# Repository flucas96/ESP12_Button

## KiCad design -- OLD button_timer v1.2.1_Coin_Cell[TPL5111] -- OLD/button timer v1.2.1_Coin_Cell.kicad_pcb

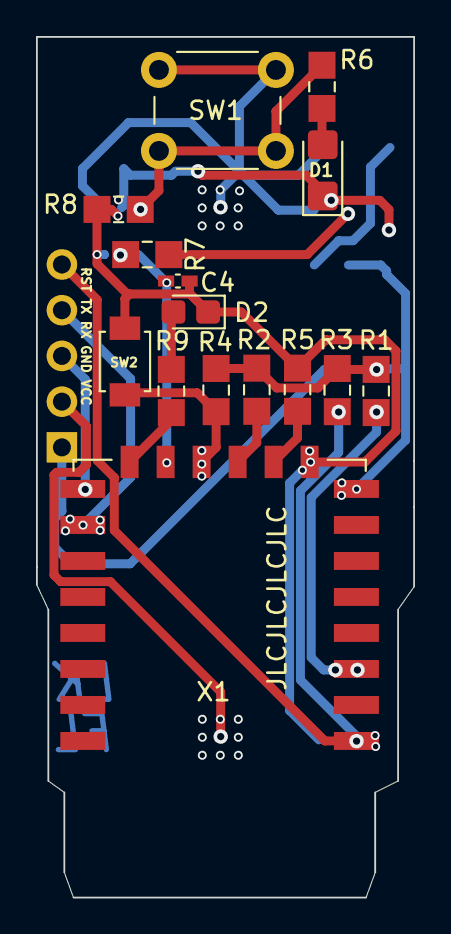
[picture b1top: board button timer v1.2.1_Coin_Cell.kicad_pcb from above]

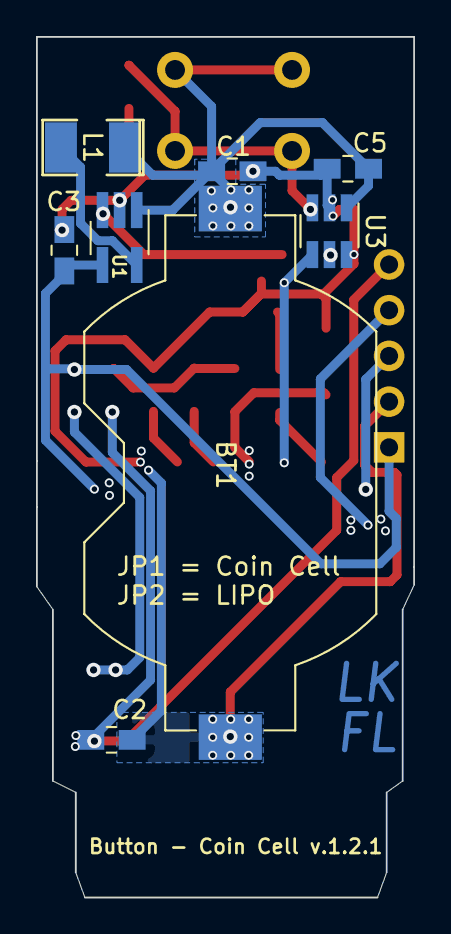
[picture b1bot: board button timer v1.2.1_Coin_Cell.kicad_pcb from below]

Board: 2 copper layers, 21.0 x 47.8 mm, 24 parts (8 on the bottom side), 18 nets.

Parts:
BT1: Battery_Cell; BatteryHolder_Keystone_1058_1x2032
C1, C3: 10uF; C_0805_2012handsodermod
C2, C5: 100nF; C_0805_2012handsodermod
C4: 10nf -100nf; C_0402_1005Metric_Pad0.74x0.62mm_HandSoldermod
D1: LED; LED_1206_3216Metric_Castellated
D2: LED; LED_0805_2012Metric_Castellated
J1: Conn_01x05_Female; PinSocket_1x05_P2.54mm_Vertical_mod
L1: 4.7 uH; SMD-1210_Pol_inductor
R1, R2, R3, R4, R7, R8: 10k; R_0805_2012handsoldermod
R5: 4.7k; R_0805_2012handsoldermod
R6, R9: 1k; R_0805_2012handsoldermod
SW1: SW_Push; SW_PUSH_6mm_H8mm_mod
SW2: SW_Push; SW_SPST_B3U-1000P_mod
U1: TPS61097A; SOT-23-5_HandSolderingmod
U3: TPL5111; SOT-23-6handsoldering
X1: ESP-12E; ESP-12Elesssilk

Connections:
/EN: R1.2, X1.3
/GND: BT1.2, C1.1, C2.1, C3.2, C4.2, C5.1, D1.1, D2.1, J1.2, R5.1, R8.1, SW2.2, U1.2, U3.2, U3.6, X1.9
/GPIO0: R4.2, SW2.1, X1.12
/GPIO2: R2.2, X1.11
/GPIO4: C4.1, U3.4, X1.13
/GPIO5: R9.2, X1.14
/GPIO15: R5.2, X1.10
/RST: C2.2, J1.5, R3.2, X1.1
/RX: J1.3, X1.15
/TX: J1.4, X1.16
/VCC: C3.1, J1.1, R1.1, R2.1, R3.1, R4.1, U1.4, X1.8
unnamed: BT1.1, C1.2, C5.2, L1.1, SW1.1, U1.1, U3.1
unnamed: D1.2, R6.1
unnamed: D2.2, R9.1
unnamed: L1.2, U1.5
unnamed: R6.2, R8.2, SW1.2, U3.3
unnamed: R7.1, U3.5
unnamed: R7.2, U1.3
